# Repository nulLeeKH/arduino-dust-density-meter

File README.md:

# arduino-dust-density-meter
The firmware for arduino which developed for an experience booth at the Science and Technology Festival Hall of the 2018 Ulsan Education Exhibition

## Info
- schematic

## H/W Spec
- Arduino uno × 1
- 1602 LCD × 1
- Sharp GP2Y1014AU0F × 1
- 220uF (capacitor) × 1
- 150ohm (resistance) × 1
- 1Kohm (resistance) × 2

## Ddependency Library
- DustDensitySensor [[Download](https://github.com/nulLeeKH/arduino-optical-dust-sensor-library)]

## Patch Note

### v1.0.0-alpha
- Initial release

### v1.1.0-alpha
- Split the DustDensitySensor library

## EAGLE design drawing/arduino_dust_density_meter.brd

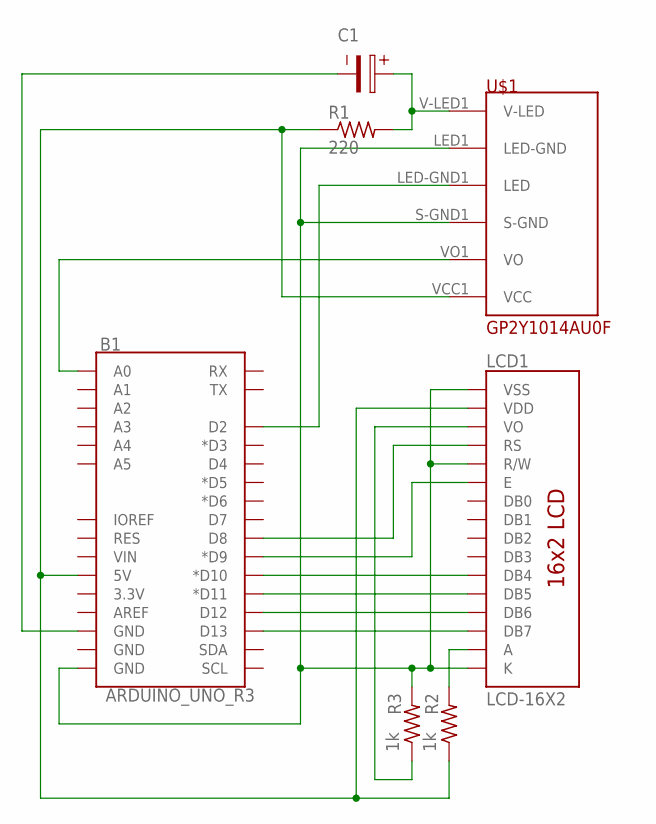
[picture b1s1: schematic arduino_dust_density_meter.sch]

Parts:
B1: ARDUINO_UNO_R3; UNO_R3_SHIELD
C1: WCAP-PTG5_10X12,5_870025575007; 10X5X0.9(DXAXB)
LCD1: LCD-16X2; LCD-16X2_NOHOLESNOSILK
R1: 220; 0309/12
R2, R3: 1k; 0309/12
U$1: GP2Y1014AU0F

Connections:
unnamed: C1.1, R1.2, U$1.V-LED1 (V-LED)
unnamed: B1.5V, LCD1.2 (VDD), R1.1, R2.1, U$1.VCC1 (VCC)
unnamed: B1.GND@2 (GND), C1.2
unnamed: B1.GND@0 (GND), LCD1.1 (VSS), LCD1.5 (R/W), LCD1.16 (K), R3.2, U$1.LED1 (LED-GND), U$1.S-GND1 (S-GND)
unnamed: B1.D2, U$1.LED-GND1 (LED)
unnamed: B1.A0, U$1.VO1 (VO)
unnamed: B1.D13, LCD1.14 (DB7)
unnamed: B1.D12, LCD1.13 (DB6)
unnamed: B1.D11 (*D11), LCD1.12 (DB5)
unnamed: B1.D10 (*D10), LCD1.11 (DB4)
unnamed: B1.D9 (*D9), LCD1.6 (E)
unnamed: B1.D8, LCD1.4 (RS)
unnamed: LCD1.15 (A), R2.2
unnamed: LCD1.3 (VO), R3.1

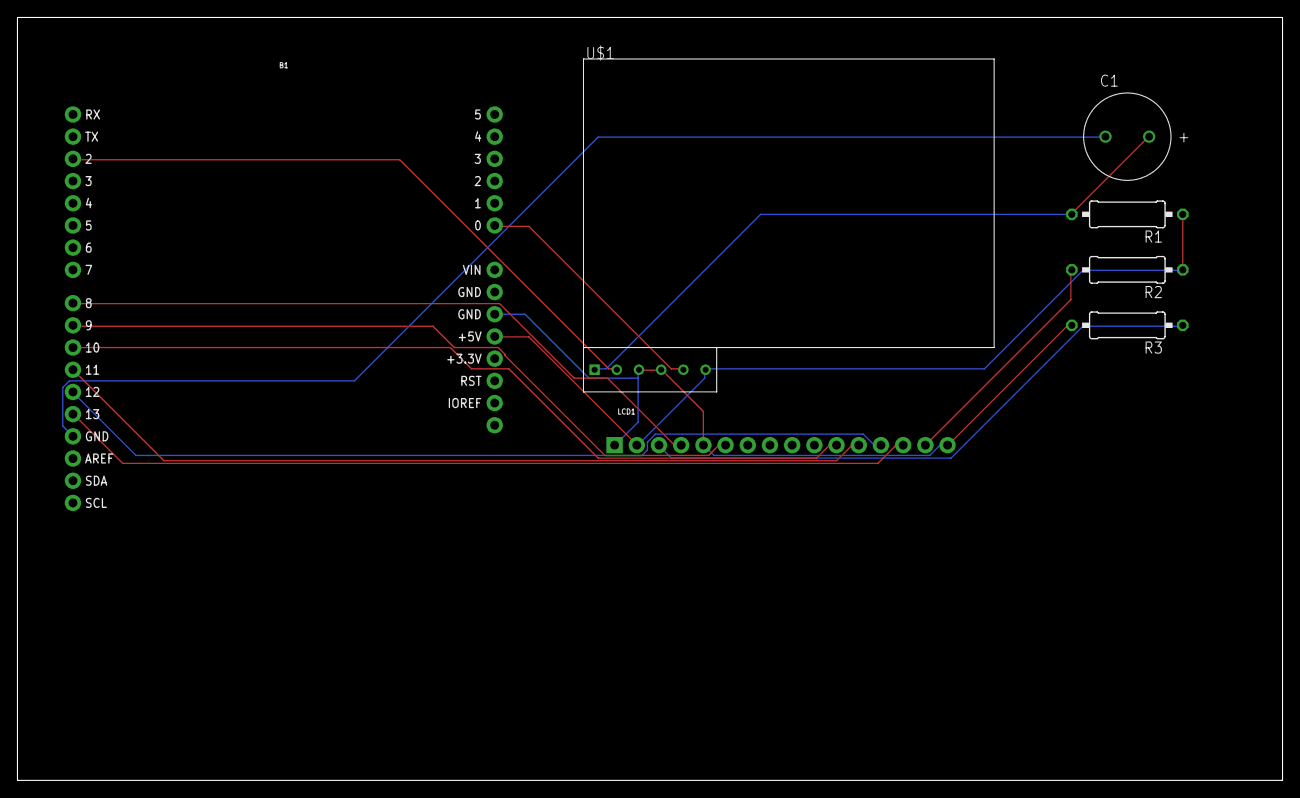
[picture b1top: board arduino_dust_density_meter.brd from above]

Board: 2 copper layers, 144.8 x 87.3 mm, 7 parts (0 on the bottom side), 14 nets.

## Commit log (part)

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2019-12-24 [INITIAL] Initial commit
2019-12-24 [UPDATE] Release v1.0.0-alpha
2019-12-24 [REFACTOR] Add patch note and license in source
2019-12-24 [UPDATE] Release v1.1.0
    Split the DustDensitySensor library.
2019-12-24 [DOCUMENT] Modify download link in README.MD
2019-12-24 [FIX] Optimize voc and sensitivity
2019-12-24 [DOCUMENT] Add H/W Spec in README.md
2019-12-24 [REFACTOR] Modify comments
2019-12-24 [DOCUMENT] Change owner information of license
2019-12-24 [REFACTOR] Change owner informaiton of license in source
2019-12-24 [DOCUMENT] Change * to × in H/W Spec in README.md
2019-12-24 [DOCUMENT] Modify texts in README.md
2019-12-24 [] Modify title and description in README.md
2019-12-24 [DOCUMENt] Modify several lines in README.md
2019-12-24 [DOCUMENT] Add schematic image in README.md
2019-12-24 [DOCUMENT] Correct word in README.md
2019-12-24 [DOCUMENT] Modify schematic for ease of viewing
2019-12-24 [REFACTOR&ADD] Change file naming rule and create board file
2019-12-24 [DOCUMENT] Fix error that README.md cannot display schematic
2019-12-24 [REFACTOR] Change sensor library
2019-12-24 [DOCUMENT] Add some badges in README.md
2019-12-24 [DOCUMENT] Move badge location in README.md
2020-02-09 [DOCUMENT] Remove '.' in description in README.md
2020-06-17 [DOCUMENT] Update LICENSE
    Reformat owner name.
    Update year range.
2020-06-19 [DOCUMENT] Apply updated license in code

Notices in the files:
parts and their libraries:
SparkFun-Boards: Licensing: Creative Commons ShareAlike 4.0 International - https://creativecommons.org/licenses/by-sa/4.0
Wurth_Elektronik_Passive_Capacitors_rev1: Copyright: Würth Elektronik
